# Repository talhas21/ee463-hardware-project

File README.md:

# ee463-hardware-project
EE463 Hardware Project Repo for 2026-2027 Fall Semester

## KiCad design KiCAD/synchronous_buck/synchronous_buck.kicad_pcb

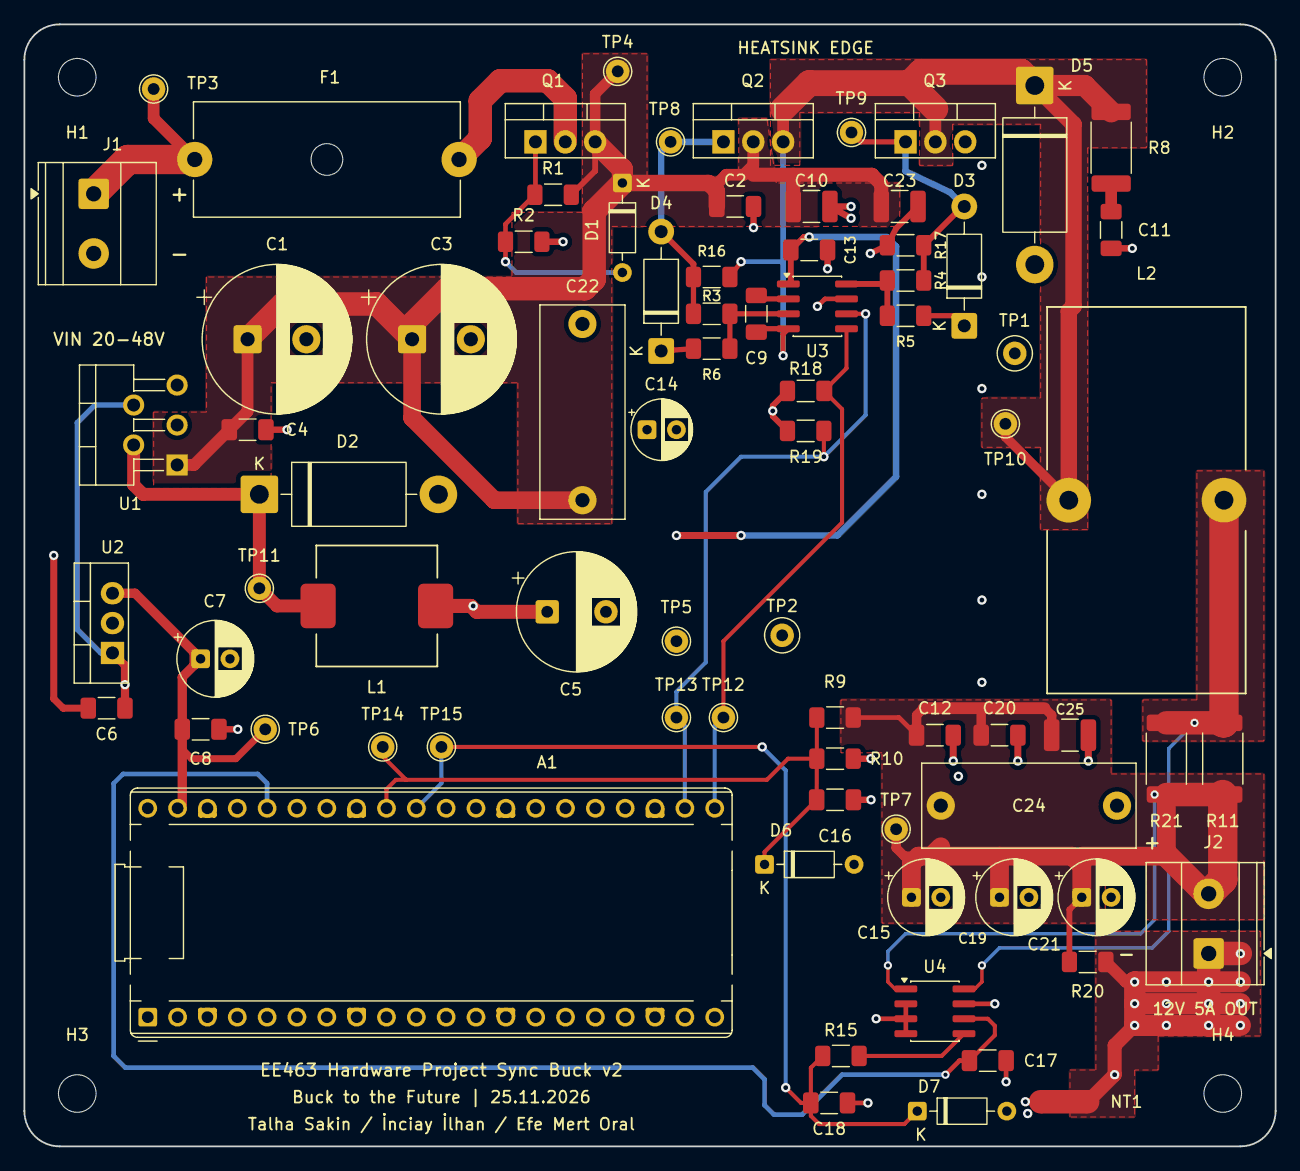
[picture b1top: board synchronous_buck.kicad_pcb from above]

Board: 4 copper layers, 106.5 x 95.5 mm, 82 parts (0 on the bottom side), 26 nets.

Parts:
A1: RaspberryPi_Pico; RaspberryPi_Pico_Common_THT
C1, C3: 100uF 100V Elec; CP_Radial_D12.5mm_P5.00mm
C2, C4: 100nF 100V X7R; C_1206_3216Metric_Pad1.33x1.80mm_HandSolder
C5: 470uF 25V Elec; CP_Radial_D10.0mm_P5.00mm
C6, C8, C13, C17: 100nF 50V X7R; C_1206_3216Metric_Pad1.33x1.80mm_HandSolder
C7, C15, C19, C21: 100uF 25V Elec; CP_Radial_D6.3mm_P2.50mm
C9: 470nF 50V X7R; C_1206_3216Metric_Pad1.33x1.80mm_HandSolder
C10: 4.7uF 100V X7R; C_1210_3225Metric_Pad1.33x2.70mm_HandSolder
C11: 1nF 100V C0G/X7R; C_1206_3216Metric_Pad1.33x1.80mm_HandSolder
C12, C20: 100nF 25V X7R; C_1206_3216Metric_Pad1.33x1.80mm_HandSolder
C14: 4.7uF 50V Elec; CP_Radial_D5.0mm_P2.50mm
C16, C18: 1nF 25V X7R; C_1206_3216Metric_Pad1.33x1.80mm_HandSolder
C22: 1uF 100V Film (DNP); C_Rect_L18.0mm_W7.0mm_P15.00mm_FKS3_FKP3
C23: 4.7uF 100V X7R (DNP); C_1210_3225Metric_Pad1.33x2.70mm_HandSolder
C24: 1uF 50V Film (DNP); C_Rect_L18.0mm_W7.0mm_P15.00mm_FKS3_FKP3
C25: 10uF 25V X7R (DNP); C_1210_3225Metric_Pad1.33x2.70mm_HandSolder
D1: BZX55C12 (12V 0.5W); D_DO-35_SOD27_P7.62mm_Horizontal
D2: SR3100 (100V 3A); D_DO-201AD_P15.24mm_Horizontal
D3, D4: 1N5819 (40V 1A); D_DO-41_SOD81_P10.16mm_Horizontal
D5: SR5100 (100V 5A); D_DO-201AD_P15.24mm_Horizontal
D6, D7: BZX55C3V3 (3.3V 0.5W); D_DO-35_SOD27_P7.62mm_Horizontal
F1: 5A 250V Slow-Blow; Fuseholder_Cylinder-5x20mm_Schurter_0031_8201_Horizontal_Op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
H1, H2, H3, H4: M3; MountingHole_3.2mm_M3
J1: VIN 20-48V 2P; TerminalBlock_Phoenix_MKDS-1,5-2-5.08_1x02_P5.08mm_Horizont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
J2: VOUT 12V 5A 2P; TerminalBlock_Phoenix_MKDS-1,5-2-5.08_1x02_P5.08mm_Horizont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
L1: 220uH 1.0A (7447714221); L_Wuerth_WE-PD_1050_HandSolder
L2: 68uH 7.7A (HCTI-68-7.7); L_Toroid_Vertical_L32.5mm_W16.5mm_P13.21mm_HCTI-68-7.7
NT1: GND_STAR_TIE; NetTie-2_SMD_Pad2.0mm
Q1: IRF5210PBF; TO-220-3_Vertical
Q2, Q3: IRFB4110; TO-220-3_Vertical
R1, R10, R16, R17, R18, R19: 10k 1% 1/4W; R_1206_3216Metric_Pad1.30x1.75mm_HandSolder
R2: 15k 1% 1/4W; R_1206_3216Metric_Pad1.30x1.75mm_HandSolder
R3, R4: 22R 1% 1/4W; R_1206_3216Metric_Pad1.30x1.75mm_HandSolder
R5, R6: 2.2R 1% 1/4W; R_1206_3216Metric_Pad1.30x1.75mm_HandSolder
R8: 4.7R 1% 1W; R_2512_6332Metric_Pad1.40x3.35mm_HandSolder
R9: 56k 1% 1/4W; R_1206_3216Metric_Pad1.30x1.75mm_HandSolder
R11: 5mR 1% 1W Shunt; R_2512_6332Metric_Pad1.40x3.35mm_HandSolder
R15: 1k 1% 1/4W; R_1206_3216Metric_Pad1.30x1.75mm_HandSolder
R20: 1k 1/4W (DNP); R_1206_3216Metric_Pad1.30x1.75mm_HandSolder
R21: 5mR 1W Shunt (DNP); R_2512_6332Metric_Pad1.40x3.35mm_HandSolder
TP1: PGND; TestPoint_Loop_D2.50mm_Drill1.0mm
TP2: DGND; TestPoint_Loop_D2.50mm_Drill1.0mm
TP3: +48V; TestPoint_THTPad_D2.0mm_Drill1.0mm
TP4: 48V_BUS; TestPoint_THTPad_D2.0mm_Drill1.0mm
TP5: +12V; TestPoint_THTPad_D2.0mm_Drill1.0mm
TP6: +5V; TestPoint_THTPad_D2.0mm_Drill1.0mm
TP7: V_OUT; TestPoint_THTPad_D2.0mm_Drill1.0mm
TP8: Q2_GATE; TestPoint_THTPad_D2.0mm_Drill1.0mm
TP9: Q3_GATE; TestPoint_THTPad_D2.0mm_Drill1.0mm
TP10: SW_NODE; TestPoint_THTPad_D2.0mm_Drill1.0mm
TP11: AUX_SW; TestPoint_THTPad_D2.0mm_Drill1.0mm
TP12: HI_PWM; TestPoint_THTPad_D2.0mm_Drill1.0mm
TP13: LO_PWM; TestPoint_THTPad_D2.0mm_Drill1.0mm
TP14: V_SENSE; TestPoint_THTPad_D2.0mm_Drill1.0mm
TP15: I_SENSE; TestPoint_THTPad_D2.0mm_Drill1.0mm
U1: LM2576HVT-12; TO-220-5_P3.4x3.7mm_StaggerOdd_Lead3.8mm_Vertical
U2: L7805CV-DG; TO-220-3_Vertical
U3: UCC27211DR; SOIC-8_3.9x4.9mm_P1.27mm
U4: TSC2011IDT; SOIC-8_3.9x4.9mm_P1.27mm

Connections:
+3V3: A1.36 (3V3), C17.1, U4.6
+5V: A1.39 (VSYS), C7.1, C8.1, TP6.1 (1_1), U2.3 (VO)
+12V: C5.1, C6.1, C13.1, C14.1, L1.2, TP5.1 (1_1), U1.4 (FB), U2.1 (VI), U3.1 (VDD)
+48V: F1.1, J1.1, TP3.1 (1_1)
/48V_BUS: C1.1, C2.1, C3.1, C4.1, C10.1, C22.1, C23.1, D1.1 (K), Q1.3 (SOURCE), Q2.2 (DRAIN), R1.1, TP4.1 (1_1), U1.1 (VIN)
/AUX_SW: D2.1 (K), L1.1, TP11.1 (1_1), U1.2 (OUT)
/HI_PWM: A1.21 (GPIO16), R18.1, TP12.1 (1_1), U3.5 (HI)
/I_SENSE: A1.31 (GPIO26_ADC0), C18.1, D7.1 (K), R15.2, TP15.1 (1_1)
/LO_PWM: A1.22 (GPIO17), R19.1, TP13.1 (1_1), U3.6 (LI)
/L_OUT: L2.2, R11.1, R21.1, U4.8
/Q2_GATE: D4.2 (A), Q2.1 (GATE), R3.1, R16.1, TP8.1 (1_1)
/Q3_GATE: D3.2 (A), Q3.1 (GATE), R4.1, R17.1, TP9.1 (1_1)
/SW_NODE: C9.2, D5.1 (K), L2.1, Q2.3 (SOURCE), Q3.2 (DRAIN), R8.2, R16.2, TP10.1 (1_1), U3.4 (HS)
/V_OUT: C12.1, C15.1, C19.1, C20.1, C21.1, C24.1, C25.1, J2.2, R9.1, R11.2, R20.1, R21.2, TP7.1 (1_1), U4.1
/V_SENSE: A1.32 (GPIO27_ADC1), C16.1, D6.1 (K), R9.2, R10.1, TP14.1 (1_1)
GND: C1.2, C2.2, C3.2, C4.2, C5.2, C6.2, C10.2, C11.2, C12.2, C13.2, C14.2, C15.2, C19.2, C20.2, C21.2, C22.2, C23.2, C24.2, C25.2, D2.2 (A), D5.2 (A), J1.2, J2.1, NT1.1, Q3.3 (SOURCE), R2.2, R17.2, R18.2, R19.2, R20.2, TP1.1 (1_1), U1.3 (GND), U1.5 (~ON/OFF), U3.7 (VSS)
GNDD: A1.3 (GND), A1.8 (GND), A1.13 (GND), A1.18 (GND), A1.23 (GND), A1.28 (GND), A1.33 (AGND), A1.38 (GND), C7.2, C8.2, C16.2, C17.2, C18.2, D6.2 (A), D7.2 (A), NT1.2, R10.2, TP2.1 (1_1), U2.2 (GND), U4.2, U4.3, U4.4, U4.7
unnamed: C11.1, R8.1
unnamed: D1.2 (A), Q1.1 (GATE), R1.2, R2.1
unnamed: D3.1 (K), R5.1
unnamed: D4.1 (K), R6.1
unnamed: F1.2, Q1.2 (DRAIN)
unnamed: C9.1, U3.2 (HB)
unnamed: R3.2, R6.2, U3.3 (HO)
unnamed: R4.2, R5.2, U3.8 (LO)
unnamed: R15.1, U4.5
